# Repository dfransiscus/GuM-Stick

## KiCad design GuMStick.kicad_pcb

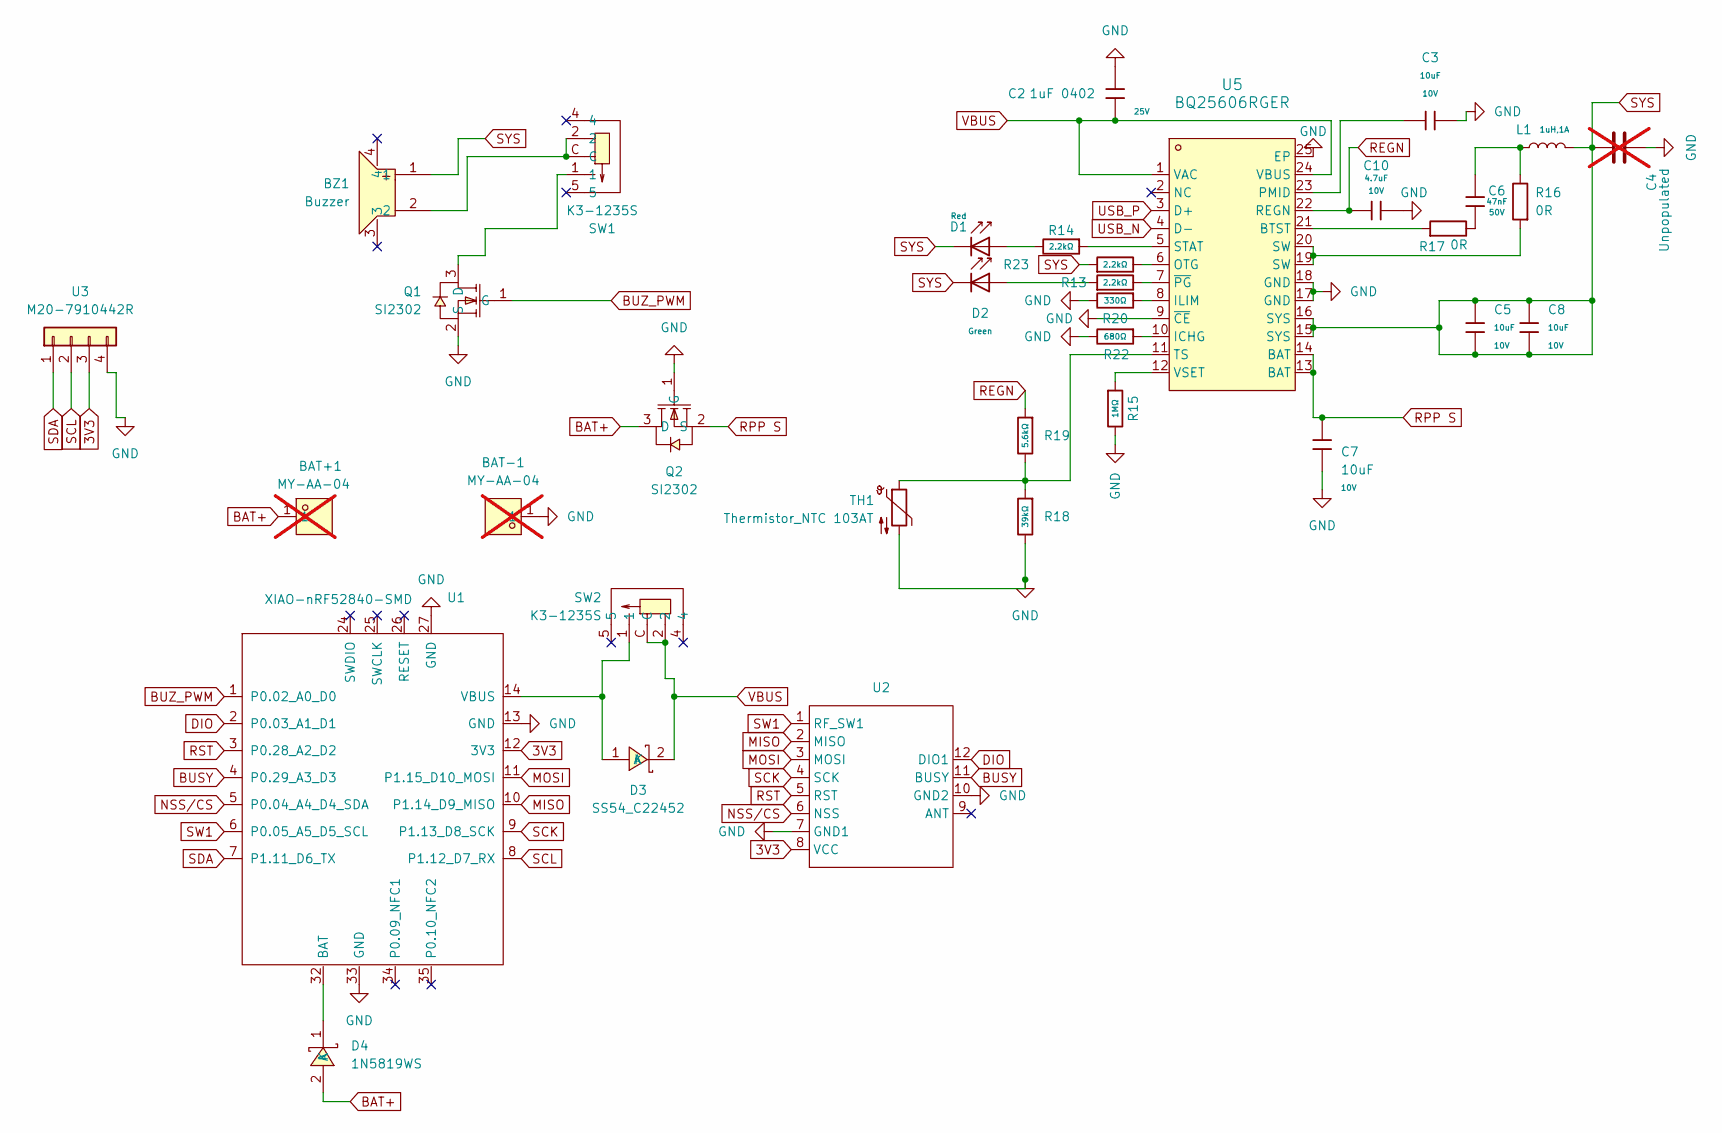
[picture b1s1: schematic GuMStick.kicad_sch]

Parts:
BAT+1: MY-AA-04; BAT-SMD_MY-AA-04; MPN MY-AA-04; LCSC Part C2979179; not fitted
BAT-1: MY-AA-04; BAT-SMD_MY-AA-04; MPN MY-AA-04; LCSC Part C2979179; not fitted
BZ1: Buzzer; BUZ-SMD_4P-L8.5-W8.5_FUET-8530-05; MPN SMD8530-32Ω; LCSC Part C49246949
C2: 1uF 0402; C_0402; Voltage Rated 25V; Tolerance ±10%; Part CL05A105KA5NQNC; LCSC C52923
C3, C5, C7, C8: 10uF; C_0603; Voltage Rated 10V; Tolerance ±10%; Part CL10A106KP8NNNC; LCSC C19702
C4: Unpopulated; C_0402_1005Metric; not fitted
C6: 47nF; C_0603; Voltage Rated 50V; Tolerance ±10%; Part CL10B473KB8NNNC; LCSC C1622
C10: 4.7uF; C_0402; Voltage Rated 10V; Tolerance ±20%; Part CL05A475MP5NRNC; LCSC C23733
D1: Red; D_0805; Forward Voltage (VF) 1.6V~2.6V; MPN NCD0805R1; LCSC C84256
D2: Green; D_0805; Part KT-0805G; LCSC C2297
D3: SS54_C22452; SMA_L4.4-W2.8-LS5.4-R-RD; MPN SS54; LCSC Part C22452
D4: 1N5819WS; SOD-323_L1.8-W1.3-LS2.5-RD; MPN 1N5819WS; LCSC Part C191023
L1: 1uH,1A; L_0805; Tolerance ±10%; Part YWLD2012-1R0K; LCSC C5339212
Q1, Q2: SI2302; SOT-23_L2.9-W1.3-P1.90-LS2.4-BR; MPN Si2302CDS-T1-GE3; LCSC Part C10488
R13, R14, R23: 2.2kΩ; R_0402; Overload Voltage (Max) 50V; Tolerance ±1%; Part 0402WGF2201TCE; LCSC C25879
R15: 1MΩ; R_0402; Overload Voltage (Max) 50V; Tolerance ±1%; Part 0402WGF1004TCE; LCSC C26083
R16, R17: 0R; R_0603; Overload Voltage (Max) 75V; Tolerance ±1%; Part 0603WAF0000T5E; LCSC C21189
R18: 39kΩ; R_0603; Overload Voltage (Max) 75V; Tolerance ±1%; Part 0603WAF3902T5E; LCSC C23153
R19: 5.6kΩ; R_0603; Overload Voltage (Max) 75V; Tolerance ±1%; Part 0603WAF5601T5E; LCSC C23189
R20: 330Ω; R_0402; Overload Voltage (Max) 50V; Tolerance ±1%; Part 0402WGF3300TCE; LCSC C25104
R22: 680Ω; R_0402; Overload Voltage (Max) 50V; Tolerance ±1%; Part 0402WGF6800TCE; LCSC C25130
SW1, SW2: K3-1235S; SW-SMD_MK-11C04-G013; MPN MK-11C04-G013; LCSC Part C778185
TH1: Thermistor_NTC 103AT; PinHeader_1x02_P2.00mm_Vertical; MPN 103AT-4-70374
U1: XIAO-nRF52840-SMD; MPN 102010448
U2: Wio-SX1262; Wio SX1262; MPN Wio-SX1262
U3: M20-7910442R; MF254RS-11-04-0743 XFCN 4 Pin Machined Header; MPN MF254RS-11-04-0743
U5: BQ25606RGER; VQFN-24_L4.0-W4.0-P0.50-TL-EP2.8; MPN BQ25606RGER; LCSC Part C374063

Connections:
3V3: U1.12 (3V3), U2.8 (VCC), U3.3
BAT+: BAT+1.1 (1_1), D4.2 (A), Q2.3 (D)
BUSY: U1.4 (P0.29_A3_D3), U2.11 (BUSY)
BUZ_PWM: Q1.1 (G), U1.1 (P0.02_A0_D0)
DIO: U1.2 (P0.03_A1_D1), U2.12 (DIO1)
GND: BAT-1.1 (1_1), C2.2, C3.1, C4.1, C7.2, C10.2, Q1.2 (S), Q2.1 (G), R15.2, R18.2, R20.2, R22.2, TH1.2, U1.13 (GND), U1.27 (GND), U1.33 (GND), U2.7 (GND1), U2.10 (GND2), U3.4, U5.9 (~CE), U5.17 (GND), U5.18 (GND), U5.25 (EP)
MISO: U1.10 (P1.14_D9_MISO), U2.2 (MISO)
MOSI: U1.11 (P1.15_D10_MOSI), U2.3 (MOSI)
NSS/CS: U1.5 (P0.04_A4_D4_SDA), U2.6 (NSS)
unnamed: BZ1.2, SW1.2, SW1.C
unnamed: C6.1, L1.1, R16.2
unnamed: C6.2, R17.2
unnamed: D1.2, R14.2
unnamed: D2.2, R13.1
unnamed: D3.1 (A), SW2.1, U1.14 (VBUS)
unnamed: D4.1 (K), U1.32 (BAT)
unnamed: Q1.3 (D), SW1.1
unnamed: R16.1, U5.19 (SW), U5.20 (SW)
unnamed: R17.1, U5.21 (BTST)
unnamed: R22.1, U5.10 (ICHG)
unnamed: R20.1, U5.8 (ILIM)
unnamed: R23.2, U5.6 (OTG)
unnamed: C3.2, U5.23 (PMID)
unnamed: R14.1, U5.5 (STAT)
unnamed: R18.1, R19.2, TH1.1, U5.11 (TS)
unnamed: R15.1, U5.12 (VSET)
unnamed: R13.2, U5.7 (~PG)
REGN: C10.1, R19.1, U5.22 (REGN)
RPP S: C7.1, Q2.2 (S), U5.13 (BAT), U5.14 (BAT)
RST: U1.3 (P0.28_A2_D2), U2.5 (RST)
SCK: U1.9 (P1.13_D8_SCK), U2.4 (SCK)
SCL: U1.8 (P1.12_D7_RX), U3.2
SDA: U1.7 (P1.11_D6_TX), U3.1
SW1: U1.6 (P0.05_A5_D5_SCL), U2.1 (RF_SW1)
SYS: BZ1.1, C4.2, C5.1, C5.2, C8.1, C8.2, D1.1, D2.1, L1.2, R23.1, U5.15 (SYS), U5.16 (SYS)
USB_N: U5.4 (D-)
USB_P: U5.3 (D+)
VBUS: C2.1, D3.2 (K), SW2.2, SW2.C, U5.1 (VAC), U5.24 (VBUS)

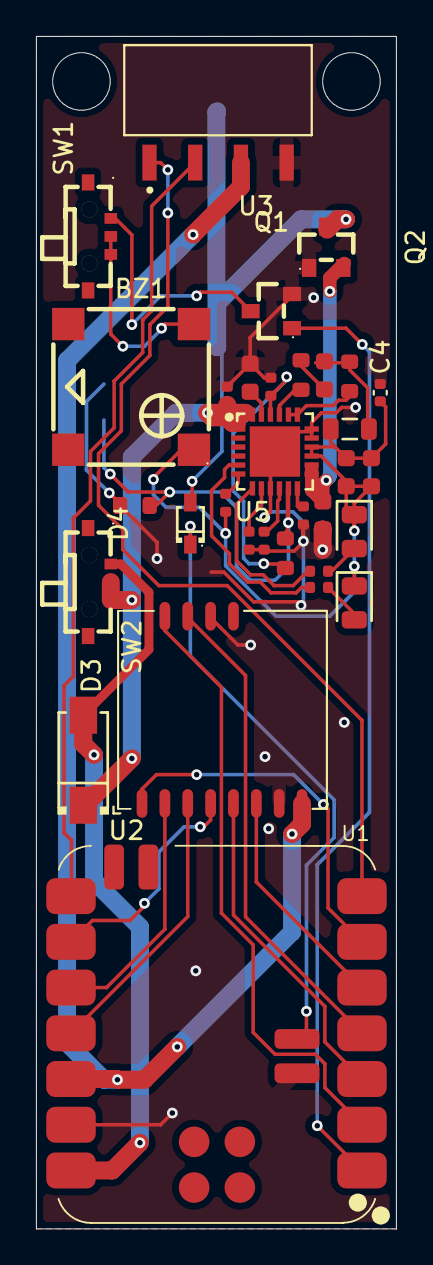
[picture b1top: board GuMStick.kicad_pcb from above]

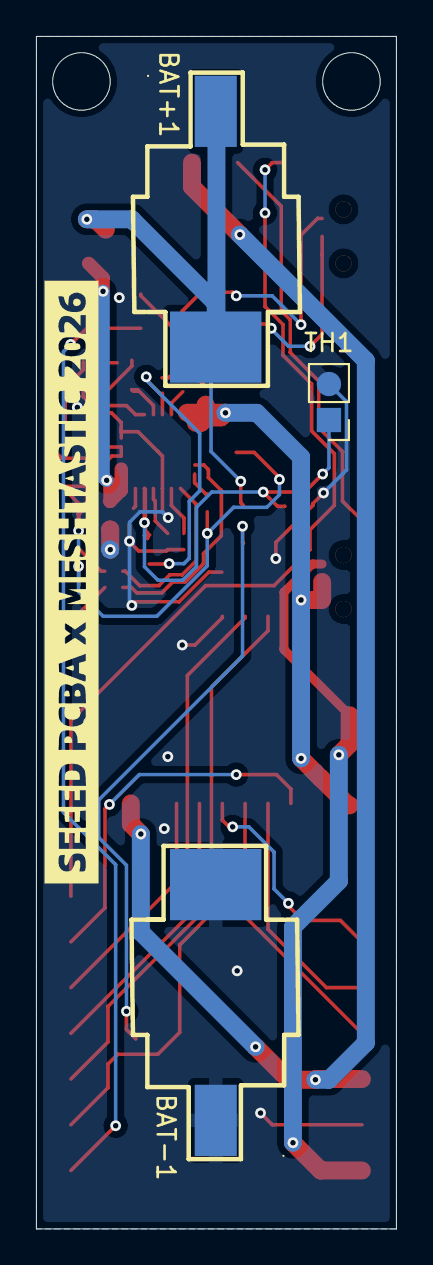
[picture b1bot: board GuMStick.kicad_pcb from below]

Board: 2 copper layers, 20.0 x 66.2 mm, 35 parts (3 on the bottom side), 36 nets.

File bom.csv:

Designator,Footprint,Quantity,Value,LCSC Part #
"BAT+1, BAT-1",BAT-SMD_MY-AA-04,2,MY-AA-04,C2979179
BZ1,BUZ-SMD_4P-L8.5-W8.5_FUET-8530-05,1,Buzzer,C49246949
C10,C_0402,1,4.7uF,C23733
C2,C_0402,1,1uF,C52923
"C3, C5, C7, C8",C_0603,4,10uF,C19702
C4,402,1,C4 DNP,
C6,C_0603,1,47nF,C1622
D1,D_0805,1,Red,C84256
D2,D_0805,1,Green,C2297
D3,SMA_L4.4-W2.8-LS5.4-R-RD,1,SS54_C22452,C22452
D4,SOD-323_L1.8-W1.3-LS2.5-RD,1,1N5819WS,C191023
L1,L_0805,1,"1uH,1A",C1042
"Q1, Q2",SOT-23_L2.9-W1.3-P1.90-LS2.4-BR,2,SI2302,C15127
"R13, R14, R23",R_0402,3,2.2kΩ,C25879
R15,R_0402,1,1MΩ,C26083
"R16, R17",R_0603,2,0R,C21189
R18,R_0603,1,39kΩ,C23153
R19,R_0603,1,5.6kΩ,C23189
R20,R_0402,1,330Ω,C25104
R22,R_0402,1,680Ω,C25130
"SW1, SW2",SW-SMD_MK-11C04-G013,2,K3-1235S,C778185
TH1,PinHeader_1x02_P2.00mm_Vertical,1,Thermistor_NTC 103AT,103AT-4-70374
U1,XIAO-nRF52840-SMD,1,XIAO-nRF52840-SMD,102010448
U2,Wio SX1262,1,Wio-SX1262,Wio-SX1262
U3,MF254RS-11-04-0743 XFCN 4 Pin Machined Header,1,M20-7910442R,MF254RS-11-04-0743
U5,VQFN-24_L4.0-W4.0-P0.50-TL-EP2.8,1,BQ25606RGER,C374063
,,,,
Case Inserts,M3*4*4.5 Heat Set Inserts,2,,
Screws,M3*10mm socket cap screws,2,,

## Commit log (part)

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2026-05-19 init
2026-06-24 Meshtastic Variant
2026-06-24 Create LICENSE
2026-06-24 Update file names, add Seeed X Meshtastic silkscreen
2026-06-26 Schematic changes, PCB changes not yet complete. Removed error with debounce capacitor in series with Bat+, should have been parallel, prevented system from working. Added a second mosfet for reverse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
